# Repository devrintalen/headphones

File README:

Headphones
----------

This is some headphones.

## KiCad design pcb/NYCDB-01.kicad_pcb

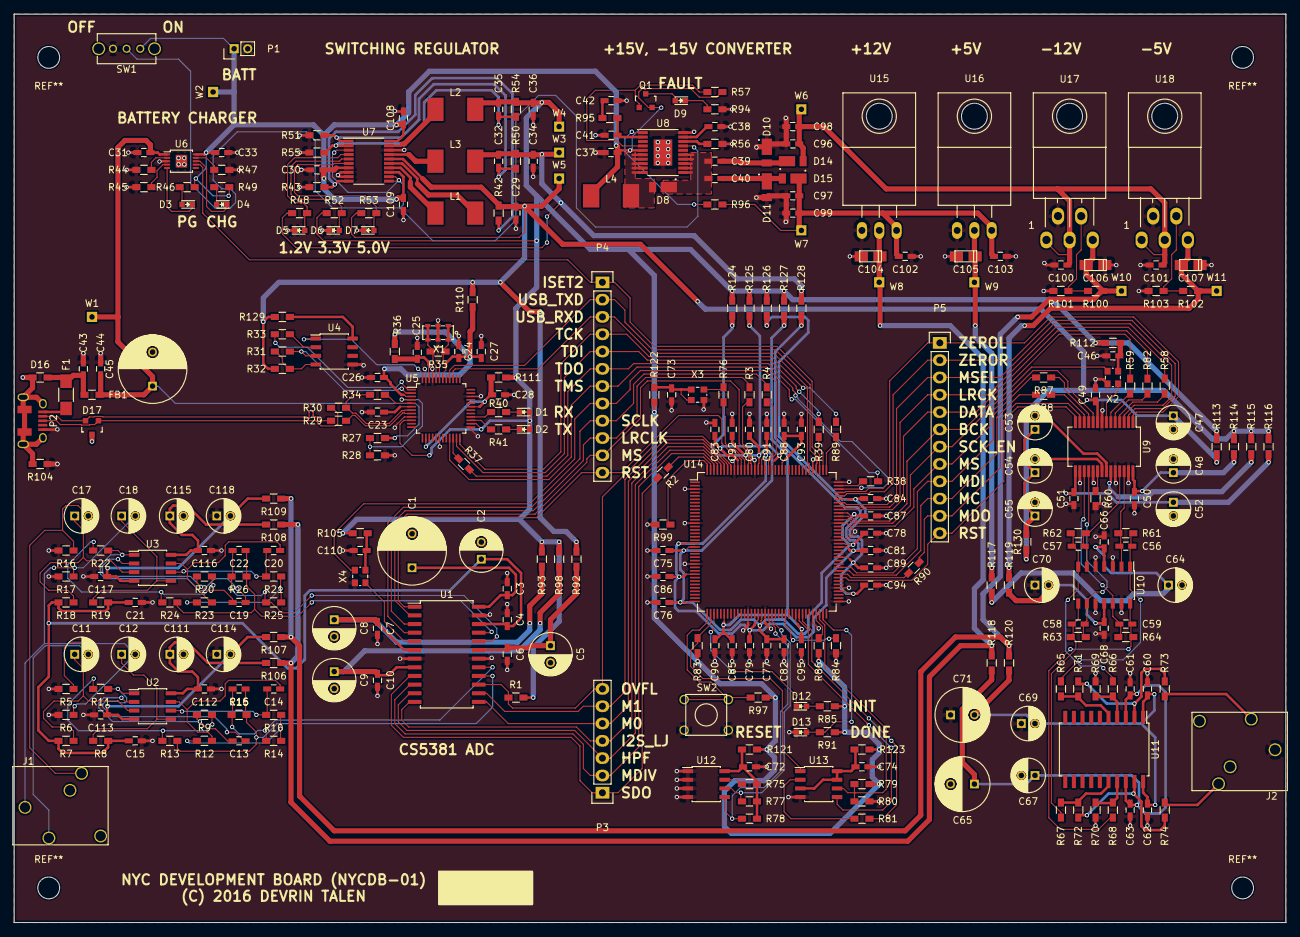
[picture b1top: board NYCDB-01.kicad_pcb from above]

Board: 2 copper layers, 186.7 x 133.3 mm, 314 parts (0 on the bottom side), 202 nets.

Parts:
C1: 220uF; C_Radial_D10_L20_P5
C2, C5, C8, C9: 1uF; C_Radial_D6.3_L11.2_P2.5
C3, C4, C6, C7, C10, C43: 0.01uF; C_0603_HandSoldering
C11, C12, C17, C18, C47, C48, C52, C55, C64, C67, C69, C70, C111, C114, C115, C118: 10uF; C_Radial_D5_L11_P2
C13, C14, C19, C20: 470pF C0G; C_0603_HandSoldering
C15, C21, C24, C25, C26, C28, C38, C44, C46, C49, C50, C51, C60, C61, C62, C63, C66, C68, C72, C73, C74, C110, C112, C113, C116, C117: 0.1uF; C_0603_HandSoldering
C16, C22: 2700pF C0G; C_0603_HandSoldering
C23: 33nF; C_0603_HandSoldering
C27, C29, C34, C36, C37, C96, C97, C98, C99, C100, C101, C102, C103: 10uF; C_0603_HandSoldering
C30, C39, C40, C75, C76, C77, C78, C79, C80, C81, C82, C83, C84, C85, C86, C87, C108, C109: 4.7uF; C_0603_HandSoldering
C31, C33: 1uF; C_0603_HandSoldering
C32: 22pF; C_0603_HandSoldering
C35: 33pF; C_0603_HandSoldering
C41: 27pF; C_0603_HandSoldering
C42: 1nF; C_0603_HandSoldering
C45: 4.7uF; C_Radial_D10_L21_P5
C53, C54: 47uF; C_Radial_D5_L11_P2
C56, C57, C58, C59: 2.7nF; C_0603_HandSoldering
C65, C71: 100uF; C_Radial_D8_L11.5_P3.5
C88, C89, C90, C91, C92, C93, C94, C95: 0.47uF; C_0603_HandSoldering
C104, C105, C106, C107: 10uF TANT; TantalC_SizeS_EIA-3216
D1: RX; LED_0603
D2: TX; LED_0603
D3: PG; LED_0603
D4: CHG; LED_0603
D5: PG1V2; LED_0603
D6: PG3V3; LED_0603
D7: PG5V0; LED_0603
D8, D10, D11, D14, D15: D; POWERDI_123
D9: FAULT15V; LED_0603
D12: INIT_B; LED_0603
D13: DONE; LED_0603
D16: V5.5MLA0603H; R_0603_HandSoldering
D17: TVS_SOT23; SOT-23
F1: 1206L150; R_1206_HandSoldering
FB1: BKP1608HS330-T; R_0603_HandSoldering
J1, J2: AUDIO_JACK; SJ1-351XN
L1, L2, L3, L4: 4.7uH; IHLP-2525CZ-01
P1: CONN_BATT; Pin_Header_Straight_1x02_Pitch2.00mm
P2: SJ110578
P3: CONN_01X07; Pin_Header_Straight_1x07
P4, P5: CONN_01X12; Pin_Header_Straight_1x12
Q1: Q_PMOS_GSD; SOT-23
R1, R7, R8, R18, R19, R28, R32, R47, R60, R77, R78: 10K; R_0603_HandSoldering
R2, R3, R4, R37, R38, R39, R58, R59, R76, R81, R82, R87, R88, R89, R90: 68; R_0603_HandSoldering
R5, R6, R16, R17, R51, R57: 100K; R_0603_HandSoldering
R9, R10, R20, R21: 634; R_0603_HandSoldering
R11, R12, R22, R23: 91; R_0603_HandSoldering
R13, R14, R15, R24, R25, R26: 200; R_0603_HandSoldering
R27, R79, R80, R85, R97: 4.7K; R_0603_HandSoldering
R29, R30: 27; R_0603_HandSoldering
R31: 2.2K; R_0603_HandSoldering
R33: 30; R_0603_HandSoldering
R34, R46, R49: 1.5K; R_0603_HandSoldering
R35: 1M; R_0603_HandSoldering
R36: 470; R_0603_HandSoldering
R40, R41: 220; R_0603_HandSoldering
R42: 121K; R_0603_HandSoldering
R43: 16.5K; R_0603_HandSoldering
R44, R45, R61, R62, R63, R64, R65, R66, R67, R68, R69, R70, R71, R72: 1K; R_0603_HandSoldering
R48, R52, R53: 294; R_0603_HandSoldering
R50: 102K; R_0603_HandSoldering
R54: 274K; R_0603_HandSoldering
R55: 60.4K; R_0603_HandSoldering
R56: 86.6K; R_0603_HandSoldering
R73, R74: 39.2; R_0603_HandSoldering
R75, R84, R86, R99, R104: 0; R_0603_HandSoldering
R83: 2.4K; R_0603_HandSoldering
R91: 330; R_0603_HandSoldering
R92, R93, R98, R105, R106, R107, R108, R109, R110, R111, R112, R113, R114, R115, R116, R117, R118, R119, R120, R121, R122, R123, R124, R125, R126, R127, R128, R129, R130: 0.1; R_0603_HandSoldering
R94: 422; R_0603_HandSoldering
R95: 34K; R_0603_HandSoldering
R96: 165K; R_0603_HandSoldering
R100: 107K; R_0603_HandSoldering
R101, R103: 12.1K; R_0603_HandSoldering
R102: 37.4K; R_0603_HandSoldering
SW1: SW_POWER; SWITCH_SPDT_OS
SW2: SW_RESET; SW_PUSH_6X6
U1: CS5361; SOIC-24_7.5x15.4mm_Pitch1.27mm
U2, U3: OP1642; SOIC-8_3.9x4.9mm_Pitch1.27mm
U4: 93CxxA; SOIC-8_3.9x4.9mm_Pitch1.27mm
U5: FT2232D; LQFP-48_7x7mm_Pitch0.5mm
U6: bq2409x; MSOP-10-1EP_3x3mm_Pitch0.5mm
U7: LTC3521; TSSOP-20_4.4x6.5mm_Pitch0.65mm
U8: LT3579; TSSOP-20_4.4x6.5mm_Pitch0.65mm_Pad
U9: PCM1792A; SSOP-28_5.3x10.2mm_Pitch0.65mm
U10: OPA4134; SOIC-14_3.9x8.7mm_Pitch1.27mm
U11: TPA6120A2; SOIC-20_7.5x12.8mm_Pitch1.27mm
U12: 24C16; SOIC-8_3.9x4.9mm_Pitch1.27mm
U13: M25P40; SOIC-8_3.9x4.9mm_Pitch1.27mm
U14: XC6SLX9TQG144; TQFP-144_20x20mm_Pitch0.5mm
U15: LT1086CT-12; TO-220_Neutral123_Horizontal
U16: LT1086CT-5; TO-220_Neutral123_Horizontal
U17, U18: LT3015ET-ADJ; Pentawatt_Neutral_Staggered-Typ1_Horizontal_TO220-5-TA05B
W1, W2, W3, W4, W5, W6, W7, W8, W9, W10, W11: TEST_1P; Measurement_Point_Square-TH_Small
X1: 6MHz; CSCTR_G
X2, X3, X4: 12.288MHz; Oscillator_SMD_2520_4Pads

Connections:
+1V2: C32.1, C34.1, L3.2, R48.1, R50.1, R128.2, W3.1
+3V3: C35.1, C36.1, D1.2, D2.2, L2.2, R1.2, R52.1, R54.1, R79.1, R83.1, R85.1, R86.1, R91.1, R93.1, R97.1, R98.1, R105.1, R111.1, R112.2, R113.2, R121.2, R122.2, R123.2, R124.2, R125.2, R126.2, R127.2, U5.10, U5.26, W4.1
+5V: C29.1, R32.1, R42.1, R53.1, R92.2, R110.2, R114.2, R115.1, R116.1, R129.2, R130.2, U7.16, W5.1
+5VA: C105.1, R117.2, U16.2, W9.1
+12VA: C104.1, R106.2, R108.2, R118.2, U15.2, W8.1
+15V: C97.1, C99.1, C102.1, C103.1, D15.1, R96.1, U15.3, U16.3, W7.1
-5VA: C107.2, R102.1, R119.1, U18.5, W11.1
-12VA: C106.2, R100.1, R107.1, R109.1, R120.1, U17.5, W10.1
-15V: C96.1, C98.1, C100.1, C101.1, D14.2, U17.1, U17.3, U18.1, U18.3, W6.1
/CS5361 ADC/ADC_HPF: P3.3, U1.11, U14.141
/CS5361 ADC/ADC_I2S_LJ: P3.4, U1.12, U14.140
/CS5361 ADC/ADC_LRCLK: P4.10, R3.2, U1.3
/CS5361 ADC/ADC_M0: P3.5, U1.13, U14.139
/CS5361 ADC/ADC_M1: P3.6, U1.14, U14.138
/CS5361 ADC/ADC_MCLK_EN: P4.8, U14.126, X4.1
/CS5361 ADC/ADC_MDIV: P3.2, U1.10, U14.142
/CS5361 ADC/ADC_MS: P4.11, U1.2, U14.132
/CS5361 ADC/ADC_OVFL: P3.7, R1.1, U1.15, U14.137
/CS5361 ADC/ADC_RST: P4.12, U1.1, U14.134
/CS5361 ADC/ADC_SCLK: P4.9, R4.2, U1.4
/CS5361 ADC/ADC_SDO: P3.1, R2.2, U1.9
/CS5361 ADC/ING: C12.2, C18.2, J1.1, R6.1, R17.1
/CS5361 ADC/INL: C11.2, J1.2, R5.1
/CS5361 ADC/INR: C17.2, J1.3, R16.1
/CS5361 ADC/left buffer/+12L: C111.1, C112.2, R106.1, U2.8
/CS5361 ADC/left buffer/-12L: C113.2, C114.2, R107.2, U2.4
/CS5361 ADC/left buffer/AIN+: C16.1, R13.1, R15.2, U1.16
/CS5361 ADC/left buffer/AIN-: C16.2, R14.1, R15.1, U1.17
/CS5361 ADC/left buffer/VQ: C2.1, C4.2, C15.2, C21.2, R7.2, R8.1, R18.2, R19.1, U1.22
/CS5361 ADC/right buffer/+12L: C115.1, C116.2, R108.1, U3.8
/CS5361 ADC/right buffer/-12L: C117.2, C118.2, R109.2, U3.4
/CS5361 ADC/right buffer/AIN+: C22.1, R24.1, R26.2, U1.21
/CS5361 ADC/right buffer/AIN-: C22.2, R25.1, R26.1, U1.20
/FT2232D/D+: D17.1, P2.3, R30.2
/FT2232D/D-: D17.2, P2.2, R29.2
/FT2232D/TCK: P4.4, R89.1, U5.24
/FT2232D/TDI: P4.5, R39.1, U5.23
/FT2232D/TDO: P4.6, R37.2, U14.106
/FT2232D/TMS: P4.7, R38.1, U5.21
/FT2232D/USB5V: C31.1, C44.2, C45.1, FB1.1, R27.2, U6.1, W1.1
/FT2232D/USBD+: R30.1, R34.1, U5.7
/FT2232D/USBD-: R29.1, U5.8
/FT2232D/USB_RXD: P4.3, U5.39, U14.114
/FT2232D/USB_TXD: P4.2, U5.40, U14.112
/Power Supplies/ISET2: P4.1, U6.7, U14.111
/Power Supplies/PWR_SW: SW1.2, U7.3, U7.11, U7.12, U8.17
/Power Supplies/V_BATT: C30.1, C33.1, C37.1, C108.1, C109.1, L4.1, P1.1, Q1.2, R46.2, R49.2, R57.2, SW1.1, U6.10, U7.7, U7.13, U7.20, U8.5, W2.1
/TI DAC/+5VL: C64.1, C66.2, R117.1, U10.4
/TI DAC/+12VL: C61.2, C63.2, C65.1, C67.1, R118.1, U11.3, U11.18
/TI DAC/-5VL: C68.2, C70.2, R119.2, U10.11
/TI DAC/-12VL: C60.2, C62.2, C69.2, C71.2, R120.2, U11.1, U11.20
/TI DAC/DAC_BCK: P5.6, R59.2, U14.99
/TI DAC/DAC_DATA: P5.5, R82.2, U14.100
/TI DAC/DAC_LRCK: P5.4, R58.2, U14.101
/TI DAC/DAC_MC: P5.10, R88.2, U14.82
/TI DAC/DAC_MDI: P5.9, R87.2, U14.83
/TI DAC/DAC_MDO: P5.11, R90.2, U9.13
/TI DAC/DAC_MS: P5.8, U9.10, U14.97
/TI DAC/DAC_MSEL: P5.3, U9.3, U14.102
/TI DAC/DAC_RST: P5.12, U9.14, U14.80
/TI DAC/DAC_SCK_EN: P5.7, U14.98, X2.1
/TI DAC/DAC_ZEROL: P5.1, U9.1, U14.105
/TI DAC/DAC_ZEROR: P5.2, U9.2, U14.104
/TI DAC/OUTL: J2.2, R73.1
/TI DAC/OUTR: J2.3, R74.1
/XC6SLX9 FPGA/VCCAUX: C75.1, C76.1, C77.1, C78.1, C80.1, C82.1, C87.1, C92.1, R124.1, U14.20, U14.36, U14.53, U14.90, U14.129
/XC6SLX9 FPGA/VCCINT: C79.1, C81.1, C86.1, C91.1, R128.1, U14.19, U14.28, U14.52, U14.89, U14.128
/XC6SLX9 FPGA/VCCO_0: C83.1, C88.1, C93.1, R125.1, U14.122, U14.125, U14.135
/XC6SLX9 FPGA/VCCO_1: C84.1, C89.1, C94.1, R126.1, U14.76, U14.86, U14.103
/XC6SLX9 FPGA/VCCO_2: C85.1, C90.1, C95.1, R127.1, U14.42, U14.63
GND: C1.2, C2.2, C3.2, C4.1, C5.2, C6.2, C7.2, C8.2, C9.2, C10.2, C15.1, C21.1, C23.2, C24.2, C25.2, C26.2, C27.2, C28.2, C29.2, C30.2, C31.2, C33.2, C34.2, C36.2, C37.2, C38.2, C41.2, C42.2, C43.2, C44.1, C45.2, C46.2, C47.2, C48.2, C49.2, C50.2, C51.2, C52.2, C55.2, C60.1, C61.1, C62.1, C63.1, C64.2, C65.2, C66.1, C67.2, C68.1, C69.1, C70.1, C71.1, C72.2, C73.2, C74.2, C75.2, C76.2, C77.2, C78.2, C79.2, C80.2, C81.2, C82.2, C83.2, C84.2, C85.2, C86.2, C87.2, C88.2, C89.2, C90.2, C91.2, C92.2, C93.2, C94.2, C95.2, C96.2, C97.2, C98.2, C99.2, C100.2, C101.2, C102.2, C103.2, C104.2, C105.2, C106.1, C107.1, C108.2, C109.2, C110.2, C111.2, C112.1, C113.1, C114.1, C115.2, C116.1, C117.1, C118.1, D5.1, D6.1, D7.1, D10.1, D11.2, D13.1, J2.1, P1.2, P2.5, R5.2, R6.2, R16.2, R17.2, R28.1, R43.2, R44.2, R45.2, R47.1, R51.2, R55.2, R56.2, R60.1, R69.1, R70.1, R80.2, R84.2, R94.2, R99.2, R101.2, R103.2, R104.1, SW1.3, SW2.2, U1.7, U1.18, U1.23, U4.5, U5.9, U5.18, U5.25, U5.34, U5.45, U5.47, U6.3, U6.11, U7.8, U7.9, U7.18, U8.20, U8.PAD, U9.8, U9.16, U9.19, U9.24, U9.27, U10.3, U10.5, U10.10, U10.13, U12.1, U12.2, U12.3, U12.4, U13.4, U14.3, U14.13, U14.25, U14.49, U14.54, U14.68, U14.73, U14.77, U14.91, U14.96, U14.108, U14.113, U14.130, U14.136, U15.1, U16.1, U17.2, U18.2, X1.2, X2.2, X3.2, X4.2
GNDPWR: D16.1, D17.3, P2.6, P2.7, P2.8, P2.9, P2.10, P2.11, R104.2
unnamed: C1.1, C3.1, U1.24
unnamed: C5.1, C6.1, R92.1, U1.19
unnamed: C7.1, C8.1, R93.2, U1.6
unnamed: C9.1, C10.1, R98.2, U1.8
unnamed: C11.1, R7.1, U2.3
unnamed: C12.1, R8.2, U2.5
unnamed: C13.1, R11.2, U2.1
unnamed: C13.2, R9.2, U2.2
unnamed: C14.1, R12.1, U2.7
unnamed: C14.2, R10.2, U2.6
unnamed: C17.1, R18.1, U3.3
unnamed: C18.1, R19.2, U3.5
unnamed: C19.1, R22.2, U3.1
unnamed: C19.2, R20.2, U3.2
unnamed: C20.1, R23.1, U3.7
unnamed: C20.2, R21.2, U3.6
unnamed: C23.1, U5.6
unnamed: C24.1, C26.1, C27.1, R36.1, R110.1, U5.3, U5.42
unnamed: C25.1, R36.2, U5.46
unnamed: C28.1, R111.2, U5.14, U5.31
unnamed: C32.2, R50.2, R51.1, U7.1
unnamed: C35.2, R54.2, R55.1, U7.2
unnamed: C38.1, U8.19
unnamed: C39.1, D10.2, D14.1
unnamed: C39.2, C40.2, D8.1, U8.11, U8.12, U8.13, U8.14, U8.15
unnamed: C40.1, D11.1, D15.2
unnamed: C41.1, R95.1, U8.2
unnamed: C42.1, R95.2
unnamed: C43.1, D16.2, F1.2, FB1.2
unnamed: C46.1, R112.1, X2.4
unnamed: C47.1, C49.1, R113.1, U9.9
unnamed: C48.1, C50.1, R114.1, U9.28
unnamed: C51.1, C52.1, R116.2, U9.15
unnamed: C53.1, C54.1, C55.1, R130.1
unnamed: C53.2, U9.22
unnamed: C54.2, U9.21
unnamed: C56.1, R61.1, R65.2, U10.1
unnamed: C56.2, R61.2, U9.26, U10.2
unnamed: C57.1, R62.1, R66.2, U10.7
unnamed: C57.2, R62.2, U9.25, U10.6
unnamed: C58.1, R63.1, R67.2, U10.8
unnamed: C58.2, R63.2, U9.18, U10.9
unnamed: C59.1, R64.1, R68.2, U10.14
unnamed: C59.2, R64.2, U9.17, U10.12
unnamed: C72.1, R75.1, R77.1, R78.1, R121.1, U12.8
unnamed: C73.1, R122.1, X3.1, X3.4
unnamed: C74.1, R123.1, U13.3, U13.7, U13.8
unnamed: C110.1, R105.2, X4.4
unnamed: D1.1, R40.1
unnamed: D2.1, R41.1
unnamed: D3.1, U6.5
unnamed: D3.2, R46.1
unnamed: D4.1, U6.8
unnamed: D4.2, R49.1
unnamed: D5.2, R48.2, U7.4
unnamed: D6.2, R52.2, U7.5
unnamed: D7.2, R53.2, U7.6
unnamed: D8.2, L4.2, U8.6, U8.7, U8.8, U8.9, U8.10
unnamed: D9.1, R94.1
unnamed: D9.2, Q1.3
unnamed: D12.1, U14.39
unnamed: D12.2, R85.2
unnamed: D13.2, R91.2, U14.71
unnamed: F1.1, P2.1
unnamed: L1.1, U7.14
unnamed: L1.2, U7.15
unnamed: L2.1, U7.19
unnamed: L3.1, U7.17
unnamed: Q1.1, R57.1, U8.4
unnamed: R2.1, U14.143
unnamed: R3.1, U14.131
unnamed: R4.1, U14.127
unnamed: R10.1, R12.2, R14.2
unnamed: R9.1, R11.1, R13.2
unnamed: R20.1, R22.1, R24.2
unnamed: R21.1, R23.2, R25.2
unnamed: R27.1, R28.2, U5.4
unnamed: R31.1, U4.3, U5.2
unnamed: R31.2, R32.2, U4.4
unnamed: R33.1, U5.1
unnamed: R33.2, U4.2
unnamed: R34.2, U5.5
unnamed: R35.1, U5.43, X1.1
unnamed: R35.2, U5.44, X1.3
unnamed: R37.1, U5.22
unnamed: R38.2, U14.107
unnamed: R39.2, U14.110
unnamed: R40.2, U5.28
unnamed: R41.2, U5.27
unnamed: R42.2, R43.1, U7.10
unnamed: R44.1, U6.2
unnamed: R45.1, U6.4
unnamed: R47.2, U6.9
unnamed: R56.1, U8.18
unnamed: R58.1, U9.4
unnamed: R59.1, U9.6
unnamed: R60.2, U9.20
unnamed: R65.1, R71.2, U11.5
unnamed: R66.1, R69.2, U11.4
unnamed: R67.1, R72.2, U11.16
unnamed: R68.1, R70.2, U11.17
unnamed: R71.1, R73.2, U11.2
unnamed: R72.1, R74.2, U11.19
unnamed: R75.2, U12.7
unnamed: R76.1, U14.133
unnamed: R76.2, X3.3
unnamed: R77.2, U12.6, U14.56
unnamed: R78.2, U12.5, U14.55
unnamed: R79.2, R80.1, U13.6, U14.70
unnamed: R81.1, U13.2
unnamed: R81.2, U14.65
unnamed: R82.1, U9.5
unnamed: R83.2, U13.1, U14.38
unnamed: R84.1, U14.60
unnamed: R86.2, U14.69
unnamed: R87.1, U9.11
unnamed: R88.1, U9.12
unnamed: R89.2, U14.109
unnamed: R90.1, U14.81
unnamed: R96.2, U8.1
unnamed: R97.2, SW2.1, U14.37
unnamed: R99.1, U14.144
unnamed: R100.2, R101.1, U17.4
unnamed: R102.2, R103.1, U18.4
unnamed: R115.2, U9.23
unnamed: R129.1, U4.8
unnamed: U1.5, X4.3
unnamed: U4.1, U5.48
unnamed: U9.7, X2.3
unnamed: U13.5, U14.64

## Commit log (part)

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2015-01-16 Initial commit
    - Includes CS4398 schematic (and output filters)
    - Includes some documentation
2015-01-18 Work in progress
    - Added CS48540 schematic, not done yet
    - Minor tweaks to CS4398 schematic
    - Fixed the origin offset for the DAC filter symbol
2015-01-18 Started adding programming header.
2015-01-18 Finished CS48540 schematic (for now) and added a doc
2015-01-18 Added GPLv3 license
2015-01-18 Added README
2015-01-18 Datasheet for the ADC
2015-01-22 Added ADC sheet based on CS5381
2015-01-25 Starting power sheet
2015-01-25 Reorganized the project directory
    - Moved all symbols to sym/
    - Created a top-level top.sch that brings together the multi-page
    schematic.
    - Brought in symbols that were previously in a different component
    library path.
2015-01-28 Filled out the top sheet a bit
2015-01-29 Beginning work on power design
2015-01-31 Added in the power design
    - Renamed the power nets throughout the design
    - Added symbols for Linear symbols
    - Added datasheets
2015-01-31 Added a power switch and battery connector
2015-01-31 Cleaned up I/O between sheets
2015-02-07 New microcontroller sheet
    - Provides control signals and I2C
    - Modified top.sym to include it
    - Added relevant docs
2015-02-09 Made a few tweaks
    - Separated the ground of the input jack from the normal ground plane
    - Added a jack detect signal out to the micro
2015-02-10 Flattened board hierarchy
2015-02-10 Cleaning up some DRC errors
2015-02-11 WIP fixing DRC errors
    - Fixed most unconnected nets
    - Fixed a lot of the net= attributes
    - Still have more DRC errors to clean up
2015-02-11 WIP fixing DRC errors
    - Fixed slot errors
    - Fixed pintype errors
2015-02-11 Re-annotated
2015-02-11 Fixed slotted refdes that I broke
2015-02-11 Adding a Makefile
2015-04-23 Added symbol for FTDI FT2232D USB IC
2015-04-23 Adding cirrus app note for output filters
2015-04-23 Added xilinx spartan 6 symbol and documentation
2015-04-23 First pass at FPGA schematic, not complete yet
2015-04-26 Initial commit of USB interface schematic
2015-04-27 Reorganizing project schematics
2015-04-27 Fixed aesthetic error with stray attribute
2015-04-27 Fixed symbols after running gsymcheck
2015-04-27 A few changes
    - Updated Makefile and project file to include the right sheets
    - Switched to grenum (rather than refdes_renum) in the Makefile
    - Ran grenum, fpga and usb_input schematics got annotated
2015-04-27 Added footprints, missing USB connector
2015-04-30 Created JAE USB footprint
2015-04-30 Ignoring .save files from grenum
2015-04-30 Added oscillator footprint
2015-05-01 Added Xilinx TQG144 footprint for FPGA
2015-05-01 Updates to the FPGA
    - Added recommended decoupling as per UG393
    - Added termination and pullup resistors to SPI flash
    - Fixed up some of the configuration pins as per UG380
    - Added I2C pullups
2015-05-02 Updated footprint choices
2015-05-02 Aesthetic fix
2015-05-02 DRC fixes for schematics
    - Fixed 1.2V netname
    - Re-annotated schematics
    - Fixed single-ended nets
    - Fixed unused slots
    There are still errors outstanding for all the unconnected pins on the
    FPGA (and others), but everything else is clean. There are warnings for
2015-07-16 Fixed footprint for FPGA
2015-07-16 Tweaked lib path for pcb
2015-07-17 Updated gitignore
2015-07-17 Began board layout
2016-01-28 Updating docs directory with latest datasheets
2016-01-28 Recording latest pcb layout work
2016-01-28 Switched to Kicad for design
    The entire schematic design has been recreated in Kicad, plus a few
    improvements.
2016-01-29 Added a second SPI device
    This second SPI slave will store the DSP program code. I've added
    it in a SPI daisy-chain with the configuration SPI device. Will
    need to do some investigating into proper termination for the MISO
    line.
2016-01-30 Revert "Added a second SPI device"
    This reverts commit 218bd654e3ca6c6a8cae487fb597d871c261f046.
    I think an i2c ROM may be more suitable.
2016-01-30 Tweaked oscillator symbol
2016-01-30 Added i2c ROM to FPGA
    This ROM is for the DSP program instructions. Other changes:
    - Increased the sheet size to 11x17
    - Moved the oscillator symbol over to bank 0
    - Repositioned the symbol blocks to spread things out
2016-01-30 Added i2c ROM datasheet
2016-01-31 Annotated schematics
2016-02-02 Simple spice sim for analog input filter
2016-02-02 Simple pspice model for the output amp stage
2016-02-02 Trying to model output load
2016-02-05 gnuplot integration for spice sim
2016-02-06 Adding more detailed op-amp sim
2016-02-06 Refactoring the spice files a bit
2016-02-06 Fixing voltage rails
2016-02-09 Ideal and opamp sims are fixed up
    These two sims now output ac and trans data to gnuplot-compatible
    .data files. They still require manual intervention to finish the
    sims. I also removed all the refactoring since it wasn't working the
    way I wanted it to.
2016-02-09 Renamed gnuplot file
2016-02-09 Improving make clean command
2016-02-09 Sims now quit on their own
2016-02-09 Polished up ADC simulations
    Looks like the cap SPICE models from TDK don't change anything much in
    the "precise" sim. Nevertheless, including them here. No load or
    input transmission line effects included yet.
2016-02-13 Picked the rest of the caps for adc_precise
2016-02-17 Taking out the adc_opamp sim
2016-02-17 Added transient analysis
    - Added transient noise source to adc_precise sim
    - Added gnuplot script to generate transient plot
2016-03-27 Adding all simulation content in the latest post
    - Updated ideal and precise models with latest sim commands
    - Added the latest gnuplot scripts
    - Updated Makefile to run everything
2016-04-05 Ditched CS4398 for TI solution
    Cirrus DAC and amp have been replaced by TI parts PCM1792A, OPA4134,
    and TPA6120A2. I followed the reference hi-fi schematic in the
    tpa6120a2 datasheet.
2016-04-05 Re-annotated schematics
2016-04-05 Added oscilator frequency
2016-04-05 Moved kicad design under pcb/
2016-04-05 Removing unused files
2016-04-05 Ignoring generated library files
2016-04-11 Cleaned up power supplies
    - Finished the FAULT LED driver
    - Annotated the schematics
    - Started updating the power consumption spreadsheet
2016-04-17 Cleaned up ERC
2016-04-18 Latest work on footprints and BOM
2016-04-19 Added more BOM info
2016-04-21 Started filling out FPGA sheet BOM
2016-04-21 Switched to microchip SPI flash
2016-04-22 Updating docs with latest components
2016-04-23 Organized docs a bit
2016-04-24 Picked components for FPGA sheet
2016-04-24 Populated BOM for DAC + amp
2016-04-27 Working through the power supplies sheet
2016-04-28 More progress on power supply sheet
2016-04-29 Picked a footprint for the inverting LDOs
2016-05-02 Finished up BOM for power supplies
2016-05-02 Tweaked USB connector schematic
2016-05-02 Swapped DNS cap for 0-ohm resistor
2016-05-06 Finished first pass at BOM
2016-05-07 Fixing up some part numbers
2016-05-07 Renamed project to NYC
2016-05-07 Fixed new ERC warning
2016-05-07 Added footprints to testpoints
2016-05-09 Began layout on board
2016-05-11 Moved some components around
2016-05-13 Began layout on power supplies
2016-05-14 Finished laying out one regulator
2016-05-14 Laid out most of the power supplies
2016-05-14 Adding CS4398 simulation
2016-05-19 Did some layout
2016-05-19 Laid out some of the ADC
    Had to flip a resistor around on the schematic to make routing a
    little cleaner, which also affected the netlist.
2016-05-20 Worked on USB connection
2016-05-21 Worked on the USB connection
2016-05-22 Moved the USB connector to a better spot
2016-05-23 Started laying out FPGA
2016-05-24 More work on the FPGA
2016-05-26 Reworking some of the ADC->FPGA traces
2016-05-26 Updated the README (finally)
2016-05-26 Fixed README extension
2016-05-26 ... and added the replacement
2016-05-27 Reordering the ADC->FPGA pins for layout
2016-05-27 Added an oscillator for the ADC
2016-05-27 Began layout on DAC
2016-05-29 Laid out most of the DAC
2016-05-29 Replaced output test pads with an audio jack
2016-05-30 Fixed placement of series termination resistors
    I had the logical placement of the series termination resistors wrong
    in the schematics (i.e. I had them placed at the source rather than
    the load) so I moved all those around to the correct sheets. I also
    moved the ADC resistors in the layout, but haven't gotten to the DAC
    ones yet.
2016-05-30 Cleaned up ADC->FPGA traces a bit
2016-05-30 Cleaned up a lot of the FT2232D->FPGA connections
    Moved the series termination resistors into the right spots and
    cleaned up and aligned all the traces to the FPGA.
2016-05-30 Connected the DAC to the FPGA
    Re-pinned out the DAC signals on the FPGA to clean up the routing and
    made all the connections. Tried to space out the traces cleanly.
2016-05-30 Starting to go through unconnected nets
2016-06-02 Starting to fix up some of the DRC errors
2016-06-03 Fixing up some tracks
2016-06-04 Cleaned up a lot of the ADC input tracks
2016-06-05 Still fixing errors
2016-06-05 Cleaned up most of the FPGA errors
2016-06-05 Cleaning up FT2232D
2016-06-05 Now cleaning up some of the DAC
2016-06-06 Cleaned up DRC errors from new 0603 footprints
2016-06-07 Added a ground plane
2016-06-08 Added some missing ground vias
2016-06-09 Tightened up the inverting regulator a bit
2016-06-10 Working on the switcher now
2016-06-11 Cleaned up the rest of the power blocks
2016-06-11 Finished cleaning up and connecting most of the power logic
2016-06-21 Fixing up USB connector
    - Had to go back through and re-annotate all the 0603 caps and
    resistors to the hand-solderding versions since those changes didn't
    make it back into the schematics the last time I tried.
    - Added a new footprint for the USB connector to connect to all the
    shield pins.
2016-08-11 Added sense resistors everywhere
2016-08-11 Still need to route all the new resistors
2016-09-17 Moving sense resistors into place
2016-09-18 Adding latest docs
2016-10-09 Cleaned up FPGA stuff a bit
2016-10-20 Finished routing power rails
2016-10-20 Finished routing everything
    There's a single unconnected net somewhere that even the DRC checker
    can't find. Not sure what to do about it.
2016-10-25 Added two more sense resistors
2016-10-29 Fixed DFM errors
    Ran the board through Advanced Circuits' freedfm.com service and
    cleaned up all the DFM warnings and errors.
2016-11-03 Added some 3D models to footprints
    The following have gotten 3D models:
    - CSCTR_G
    - IHLP-2525CZ-01
    - POWERDI_123
    - SJ1-351XN
    - SJ110578
2016-11-05 Finished adding 3d models
    Added the following:
    - B3F-1000
    - DX4R005JJ2
    - OS-102011
    Also added some documentation for the slide switch and updated the
    layout to use the new footprints. I moved the USB connector a bit
2016-11-06 3D model updates
    Moved 3D files out to the system packages3d/ folder instead of local to
    the project.
2016-11-06 Reloaded updated footprints on board
    Reloaded the footprints that I just modified the 3d models for so they
    show up.
2016-11-07 Cleanup and added testpoints
    Cleaned up some of the schematic layout without changing any nets. Also
    added testpoints to all the power rails for easy debug.
2016-11-07 Ran DRC and added some more notes
2017-02-10 Adjusted USB diff pair spacing
    Based on a 32mil board the spacing actually needs to be about 16mil to
    hit the 90ohm impedance.
2017-02-10 Ignore generated board files
2017-02-11 Traces on a plane
    - Finished placing testpoints and got footprints for them
    - Cleaned up the last of the unconnected tracks
    - Switched up supply rails for PWRGOOD LEDs
2017-02-21 Added mounting holes to the board

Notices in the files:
pcb/NYCDB-01.kicad_pcb:
(C) 2016 DEVRIN TALEN
